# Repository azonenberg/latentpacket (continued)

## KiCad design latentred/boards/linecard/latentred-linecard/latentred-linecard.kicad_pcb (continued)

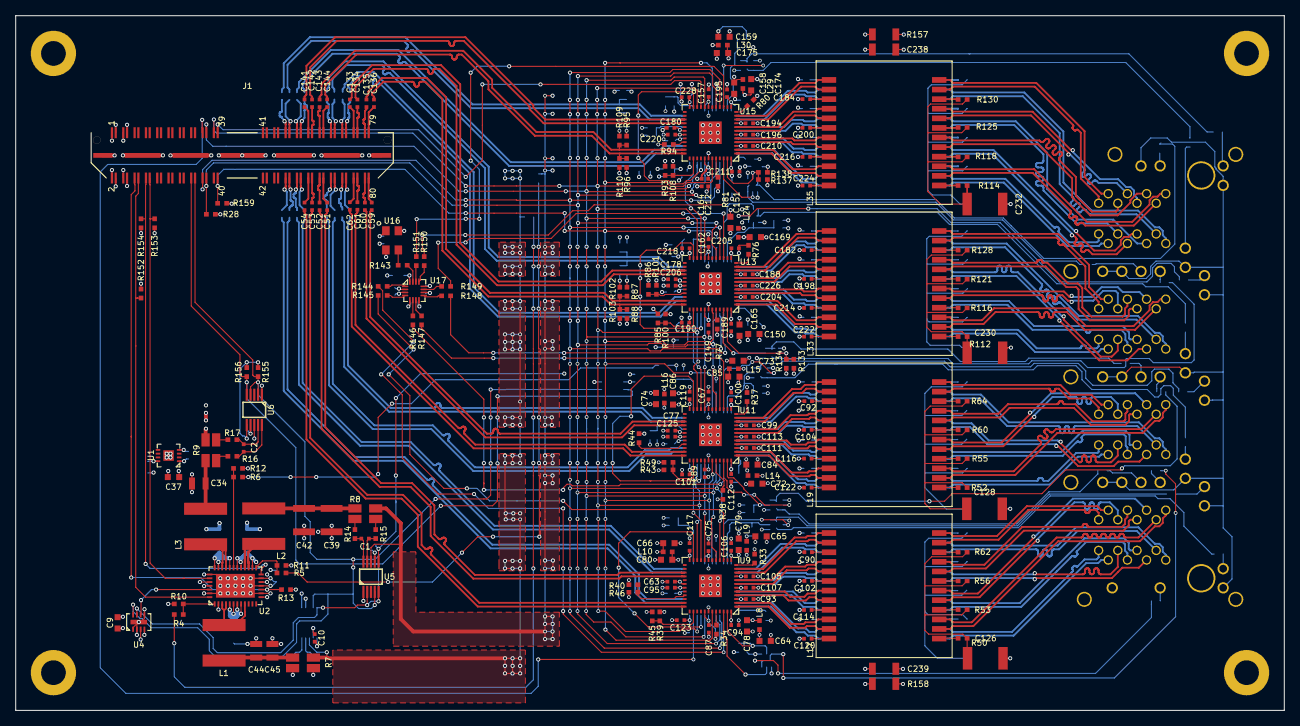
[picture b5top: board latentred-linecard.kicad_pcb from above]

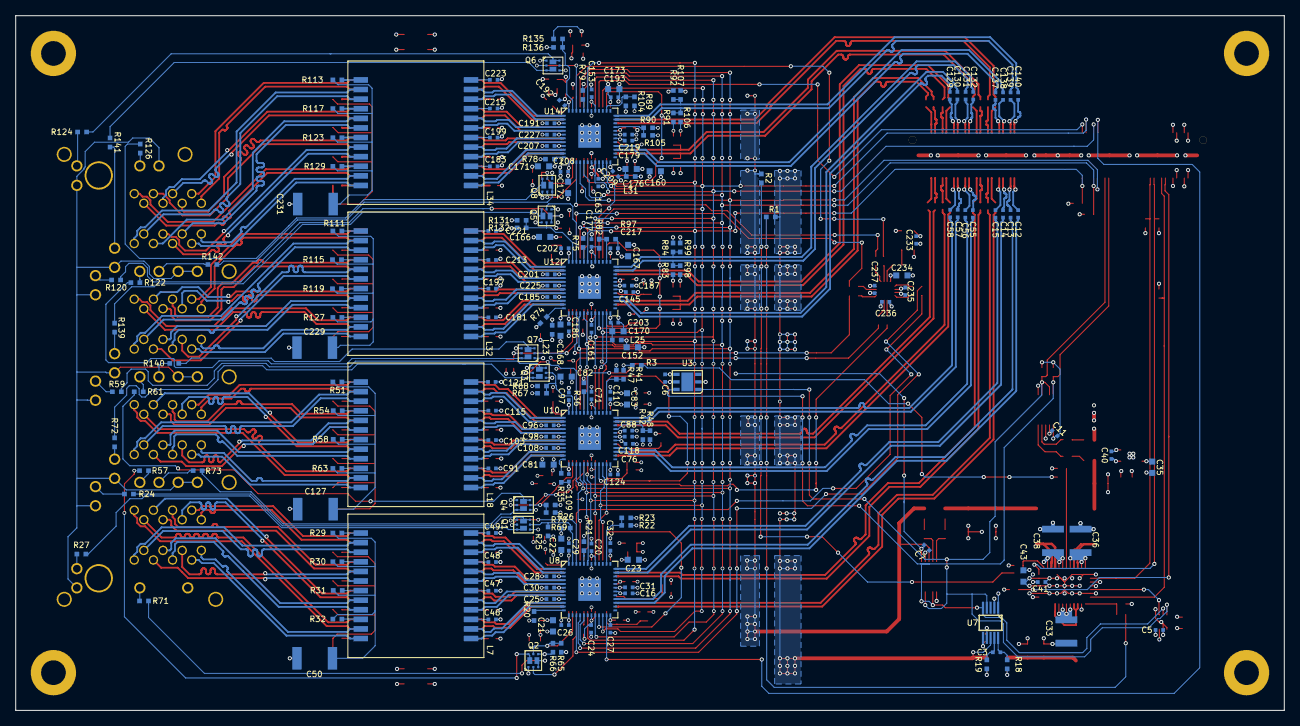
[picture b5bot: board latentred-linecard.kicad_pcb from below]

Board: 4 copper layers, 168.0 x 92.0 mm, 438 parts (211 on the bottom side), 425 nets.

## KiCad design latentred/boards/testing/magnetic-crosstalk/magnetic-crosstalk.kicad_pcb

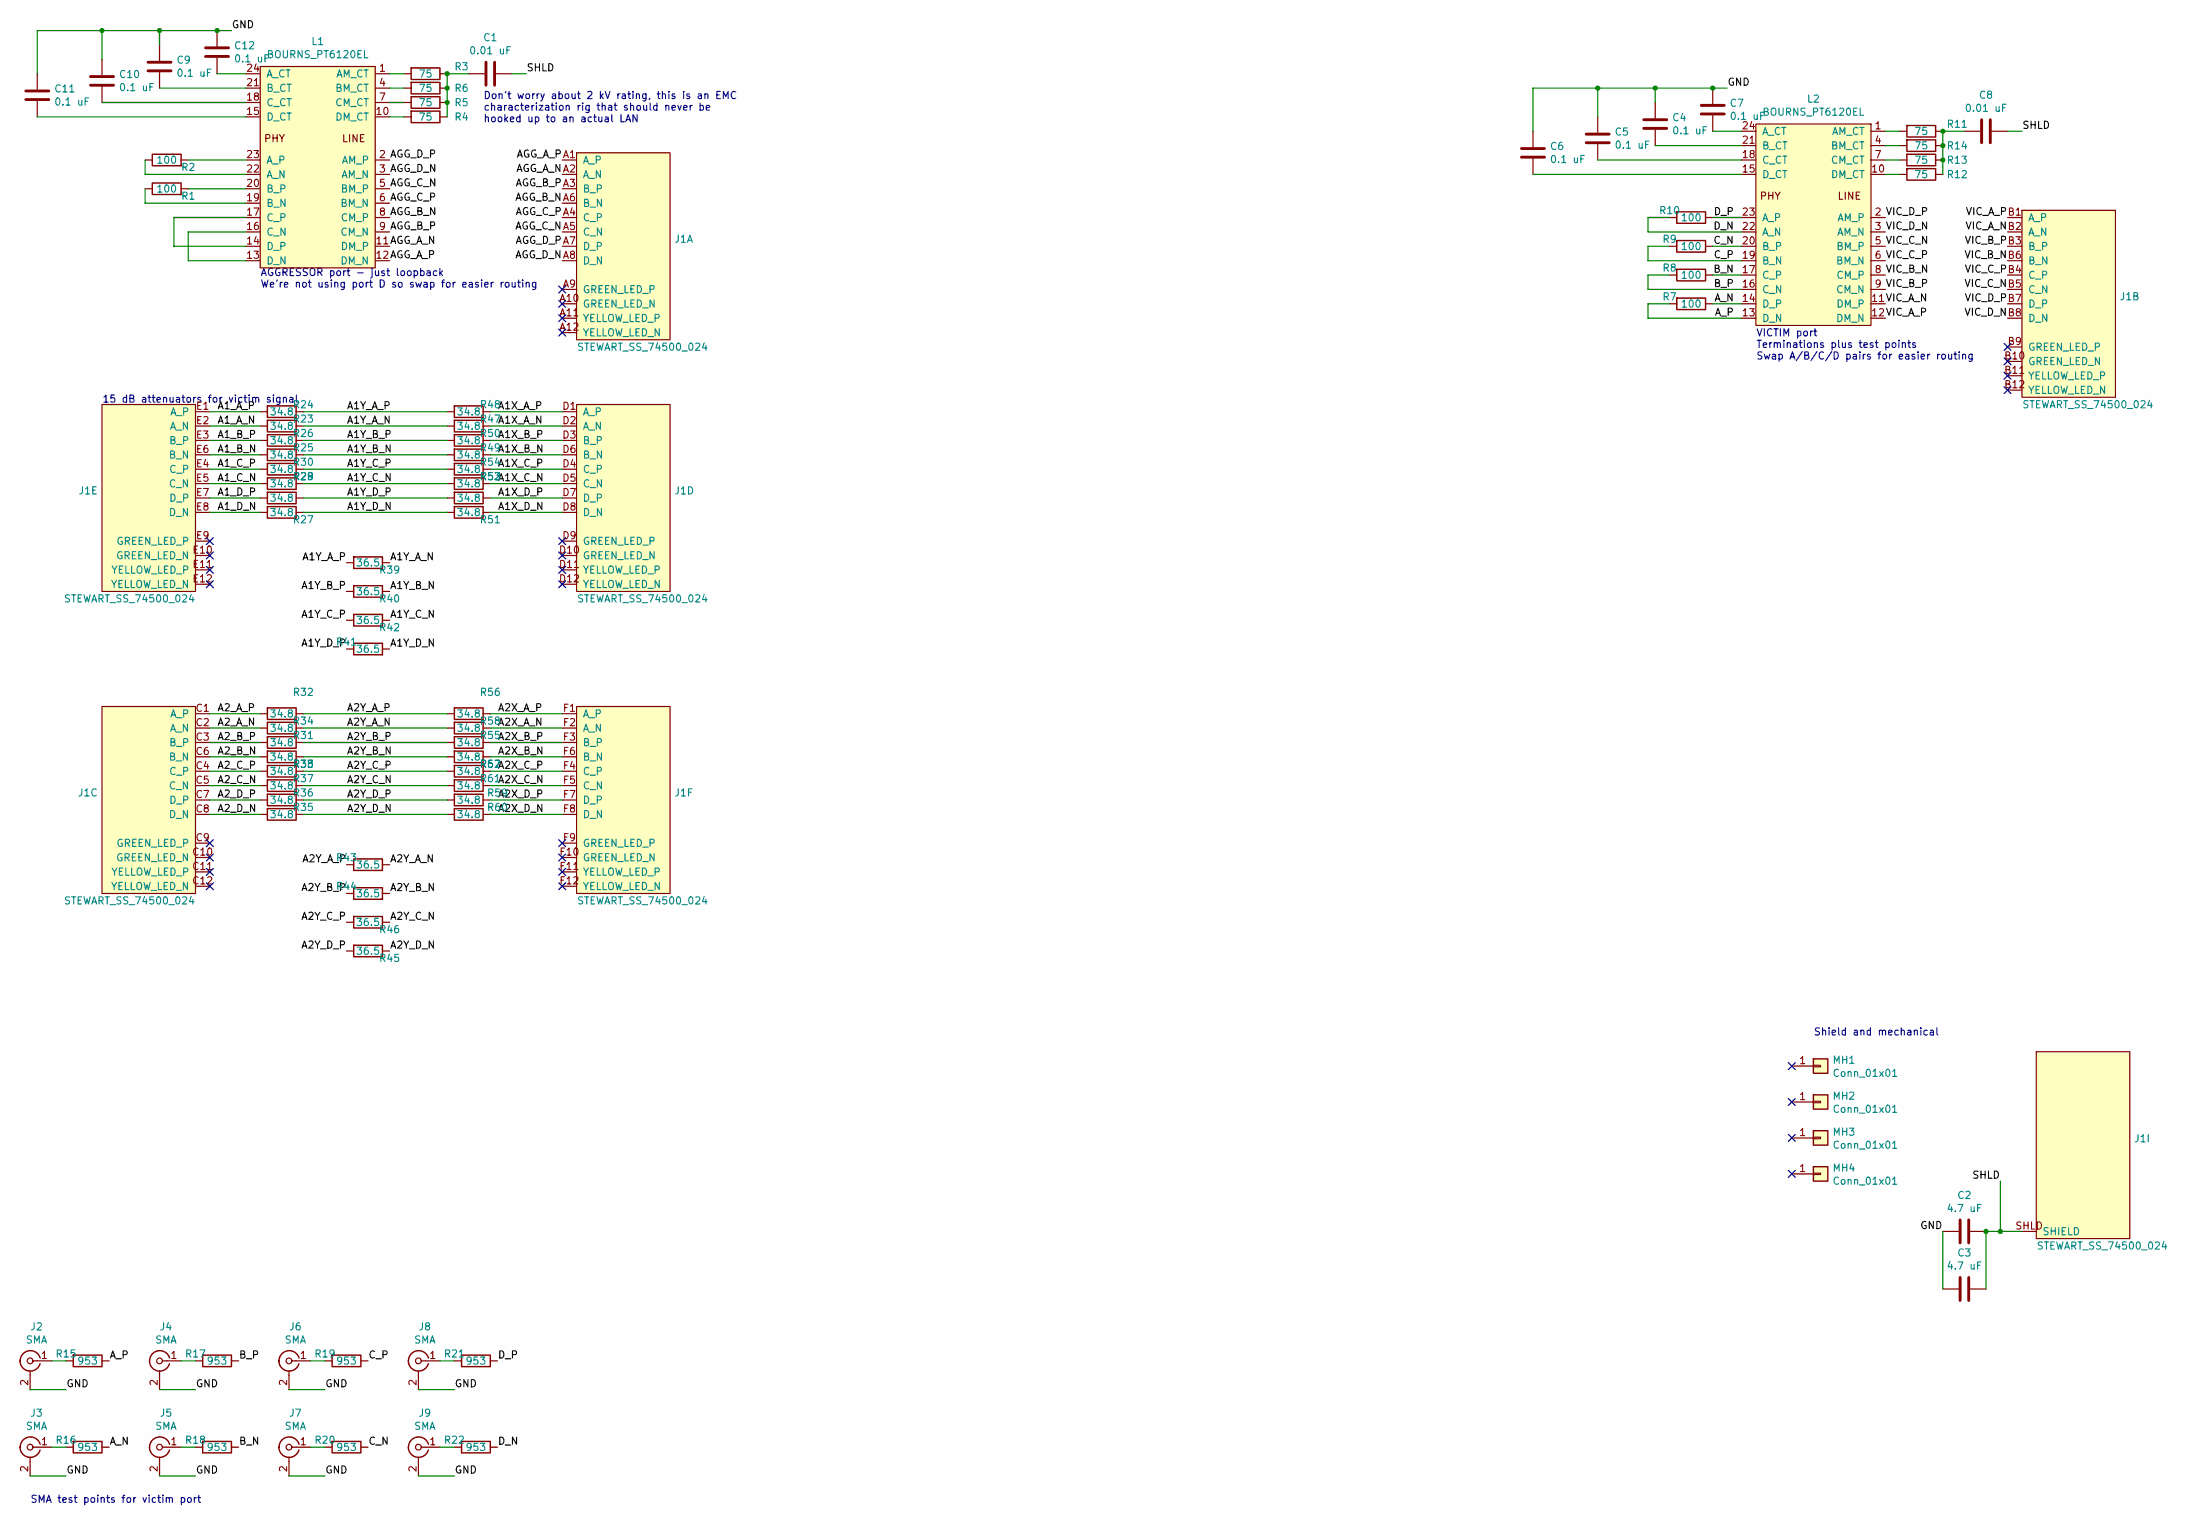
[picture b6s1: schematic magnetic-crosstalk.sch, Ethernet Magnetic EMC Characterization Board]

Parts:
C1, C8: 0.01 uF; EIA_0402_CAP_NOSILK
C2, C3: 4.7 uF; EIA_0603_CAP_NOSILK
C4, C5, C6, C7, C9, C10, C11, C12: 0.1 uF; EIA_0402_CAP_NOSILK
J1: STEWART_SS_74500_024; CONN_STEWART_SS_74500_024
J2, J3, J4, J5, J6, J7, J8, J9: SMA; CONN_SMA_EDGE_SAMTEC_SMA_J_P_H_ST_EM1
L1, L2: BOURNS_PT6120EL; BOURNS_PT61020EL
MH1, MH2, MH3, MH4: Conn_01x01; MECHANICAL_CLEARANCEHOLE_4_40
R1, R2, R7, R8, R9, R10: 100; EIA_0402_RES_NOSILK
R3, R4, R5, R6, R11, R12, R13, R14: 75; EIA_0402_RES_NOSILK
R15, R16, R17, R18, R19, R20, R21, R22: 953; EIA_0402_RES_NOSILK
R23, R24, R25, R26, R27, R28, R29, R30, R31, R32, R33, R34, R35, R36, R37, R38, R47, R48, R49, R50, R51, R52, R53, R54, R55, R56, R57, R58, R59, R60, R61, R62: 34.8; EIA_0402_RES_NOSILK
R39, R40, R41, R42, R43, R44, R45, R46: 36.5; EIA_0402_RES_NOSILK

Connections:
/A1X_A_N: J1.D2 (A_N), R48.1
/A1X_A_P: J1.D1 (A_P), R47.1
/A1X_B_N: J1.D6 (B_N), R50.1
/A1X_B_P: J1.D3 (B_P), R49.1
/A1X_C_N: J1.D5 (C_N), R54.1
/A1X_C_P: J1.D4 (C_P), R53.1
/A1X_D_N: J1.D8 (D_N), R51.1
/A1X_D_P: J1.D7 (D_P), R52.1
/A1Y_A_N: R24.1, R39.1, R48.2
/A1Y_A_P: R23.1, R39.2, R47.2
/A1Y_B_N: R26.1, R40.1, R50.2
/A1Y_B_P: R25.1, R40.2, R49.2
/A1Y_C_N: R30.1, R42.1, R54.2
/A1Y_C_P: R29.1, R42.2, R53.2
/A1Y_D_N: R27.1, R41.2, R51.2
/A1Y_D_P: R28.1, R41.1, R52.2
/A1_A_N: J1.E2 (A_N), R24.2
/A1_A_P: J1.E1 (A_P), R23.2
/A1_B_N: J1.E6 (B_N), R26.2
/A1_B_P: J1.E3 (B_P), R25.2
/A1_C_N: J1.E5 (C_N), R30.2
/A1_C_P: J1.E4 (C_P), R29.2
/A1_D_N: J1.E8 (D_N), R27.2
/A1_D_P: J1.E7 (D_P), R28.2
/A2X_A_N: J1.F2 (A_N), R55.1
/A2X_A_P: J1.F1 (A_P), R56.1
/A2X_B_N: J1.F6 (B_N), R57.1
/A2X_B_P: J1.F3 (B_P), R58.1
/A2X_C_N: J1.F5 (C_N), R62.1
/A2X_C_P: J1.F4 (C_P), R61.1
/A2X_D_N: J1.F8 (D_N), R60.1
/A2X_D_P: J1.F7 (D_P), R59.1
/A2Y_A_N: R31.1, R43.2, R55.2
/A2Y_A_P: R32.1, R43.1, R56.2
/A2Y_B_N: R33.1, R44.2, R57.2
/A2Y_B_P: R34.1, R44.1, R58.2
/A2Y_C_N: R38.1, R46.1, R62.2
/A2Y_C_P: R37.1, R46.2, R61.2
/A2Y_D_N: R36.1, R45.1, R60.2
/A2Y_D_P: R35.1, R45.2, R59.2
/A2_A_N: J1.C2 (A_N), R31.2
/A2_A_P: J1.C1 (A_P), R32.2
/A2_B_N: J1.C6 (B_N), R33.2
/A2_B_P: J1.C3 (B_P), R34.2
/A2_C_N: J1.C5 (C_N), R38.2
/A2_C_P: J1.C4 (C_P), R37.2
/A2_D_N: J1.C8 (D_N), R36.2
/A2_D_P: J1.C7 (D_P), R35.2
/AGG_A_N: J1.A2 (A_N), L1.11 (DM_P)
/AGG_A_P: J1.A1 (A_P), L1.12 (DM_N)
/AGG_B_N: J1.A6 (B_N), L1.8 (CM_P)
/AGG_B_P: J1.A3 (B_P), L1.9 (CM_N)
/AGG_C_N: J1.A5 (C_N), L1.5 (BM_P)
/AGG_C_P: J1.A4 (C_P), L1.6 (BM_N)
/AGG_D_N: J1.A8 (D_N), L1.3 (AM_N)
/AGG_D_P: J1.A7 (D_P), L1.2 (AM_P)
/A_N: L2.14 (D_P), R7.1, R16.1
/A_P: L2.13 (D_N), R7.2, R15.1
/B_N: L2.17 (C_P), R8.1, R18.1
/B_P: L2.16 (C_N), R8.2, R17.1
/C_N: L2.20 (B_P), R9.1, R20.1
/C_P: L2.19 (B_N), R9.2, R19.1
/D_N: L2.22 (A_N), R10.2, R22.1
/D_P: L2.23 (A_P), R10.1, R21.1
/GND: C2.2, C3.2, C4.1, C5.1, C6.1, C7.1, C9.1, C10.1, C11.1, C12.1, J2.2 (Ext), J3.2 (Ext), J4.2 (Ext), J5.2 (Ext), J6.2 (Ext), J7.2 (Ext), J8.2 (Ext), J9.2 (Ext)
/SHLD: C1.1, C2.1, C3.1, C8.1, J1.SHLD (SHIELD)
/VIC_A_N: J1.B2 (A_N), L2.11 (DM_P)
/VIC_A_P: J1.B1 (A_P), L2.12 (DM_N)
/VIC_B_N: J1.B6 (B_N), L2.8 (CM_P)
/VIC_B_P: J1.B3 (B_P), L2.9 (CM_N)
/VIC_C_N: J1.B5 (C_N), L2.5 (BM_P)
/VIC_C_P: J1.B4 (C_P), L2.6 (BM_N)
/VIC_D_N: J1.B8 (D_N), L2.3 (AM_N)
/VIC_D_P: J1.B7 (D_P), L2.2 (AM_P)
unnamed: C1.2, R3.1, R4.1, R5.1, R6.1
unnamed: C4.2, L2.21 (B_CT)
unnamed: C5.2, L2.18 (C_CT)
unnamed: C6.2, L2.15 (D_CT)
unnamed: C7.2, L2.24 (A_CT)
unnamed: C8.2, R11.1, R12.1, R13.1, R14.1
unnamed: C9.2, L1.21 (B_CT)
unnamed: C10.2, L1.18 (C_CT)
unnamed: C11.2, L1.15 (D_CT)
unnamed: C12.2, L1.24 (A_CT)
unnamed: J2.1 (In), R15.2
unnamed: J3.1 (In), R16.2
unnamed: J4.1 (In), R17.2
unnamed: J5.1 (In), R18.2
unnamed: J6.1 (In), R19.2
unnamed: J7.1 (In), R20.2
unnamed: J8.1 (In), R21.2
unnamed: J9.1 (In), R22.2
unnamed: L1.1 (AM_CT), R3.2
unnamed: L1.4 (BM_CT), R6.2
unnamed: L1.7 (CM_CT), R5.2
unnamed: L1.10 (DM_CT), R4.2
unnamed: L1.13 (D_N), L1.16 (C_N)
unnamed: L1.14 (D_P), L1.17 (C_P)
unnamed: L1.19 (B_N), R1.1
unnamed: L1.20 (B_P), R1.2
unnamed: L1.22 (A_N), R2.1
unnamed: L1.23 (A_P), R2.2
unnamed: L2.1 (AM_CT), R11.2
unnamed: L2.4 (BM_CT), R14.2
unnamed: L2.7 (CM_CT), R13.2
unnamed: L2.10 (DM_CT), R12.2

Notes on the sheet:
AGGRESSOR port - just loopback We're not using port D so swap for easier routing
Don't worry about 2 kV rating, this is an EMC characterization rig that should never be hooked up to an actual LAN
VICTIM port Terminations plus test points Swap A/B/C/D pairs for easier routing
15 dB attenuators for victim signal
Shield and mechanical
SMA test points for victim port

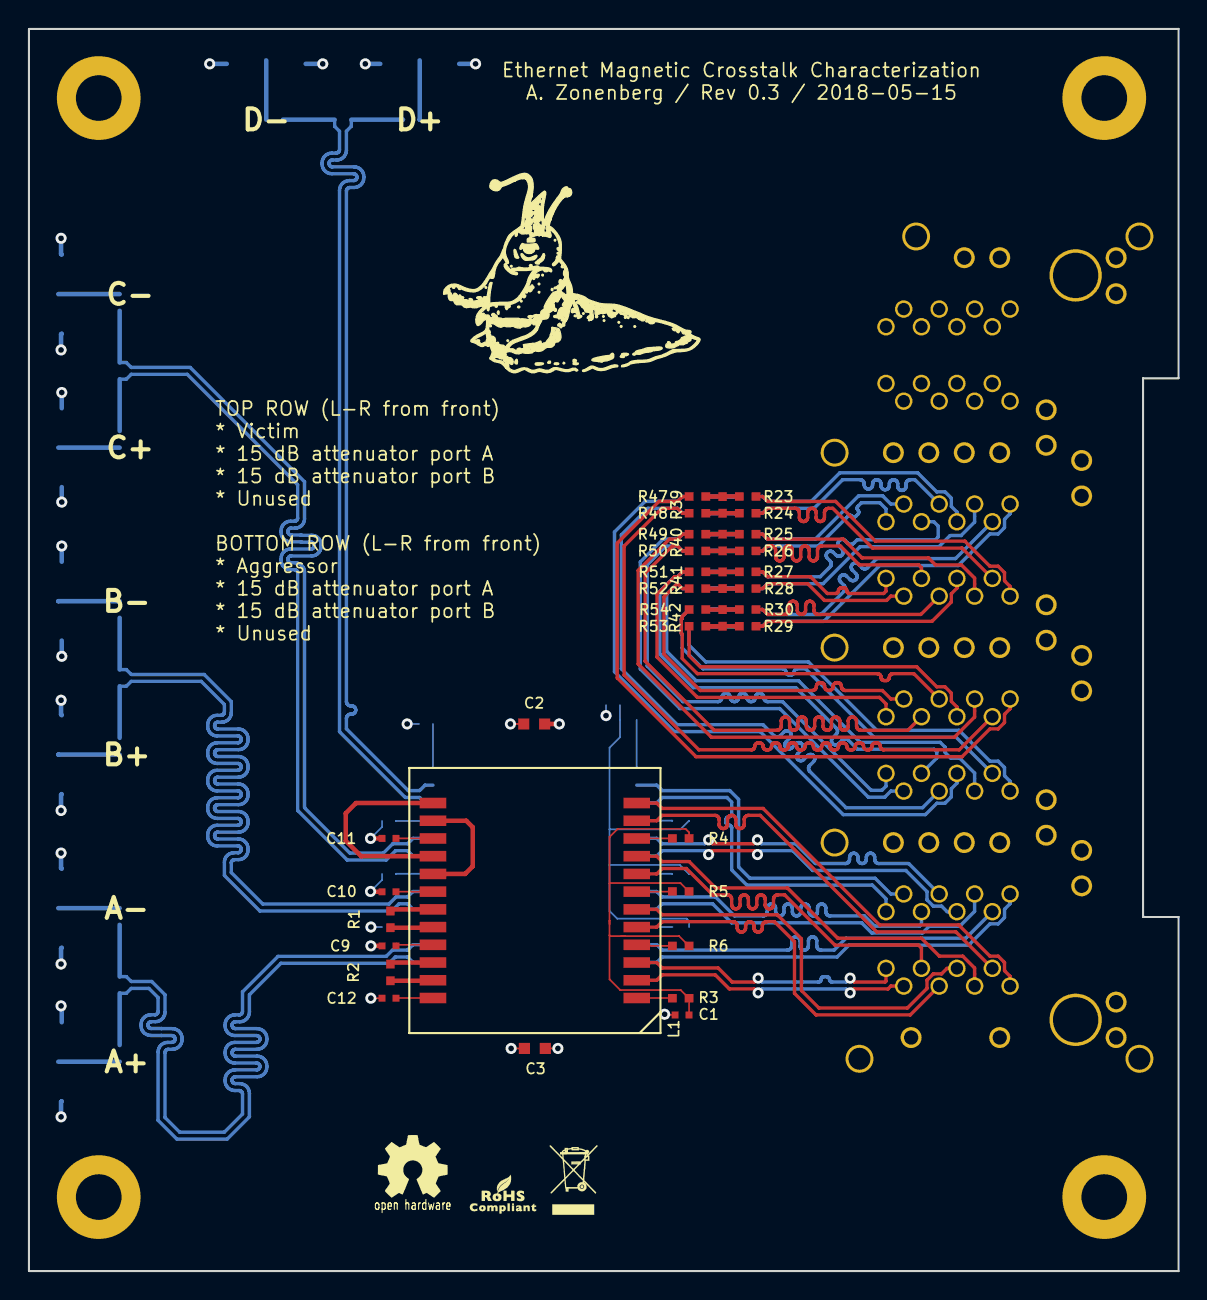
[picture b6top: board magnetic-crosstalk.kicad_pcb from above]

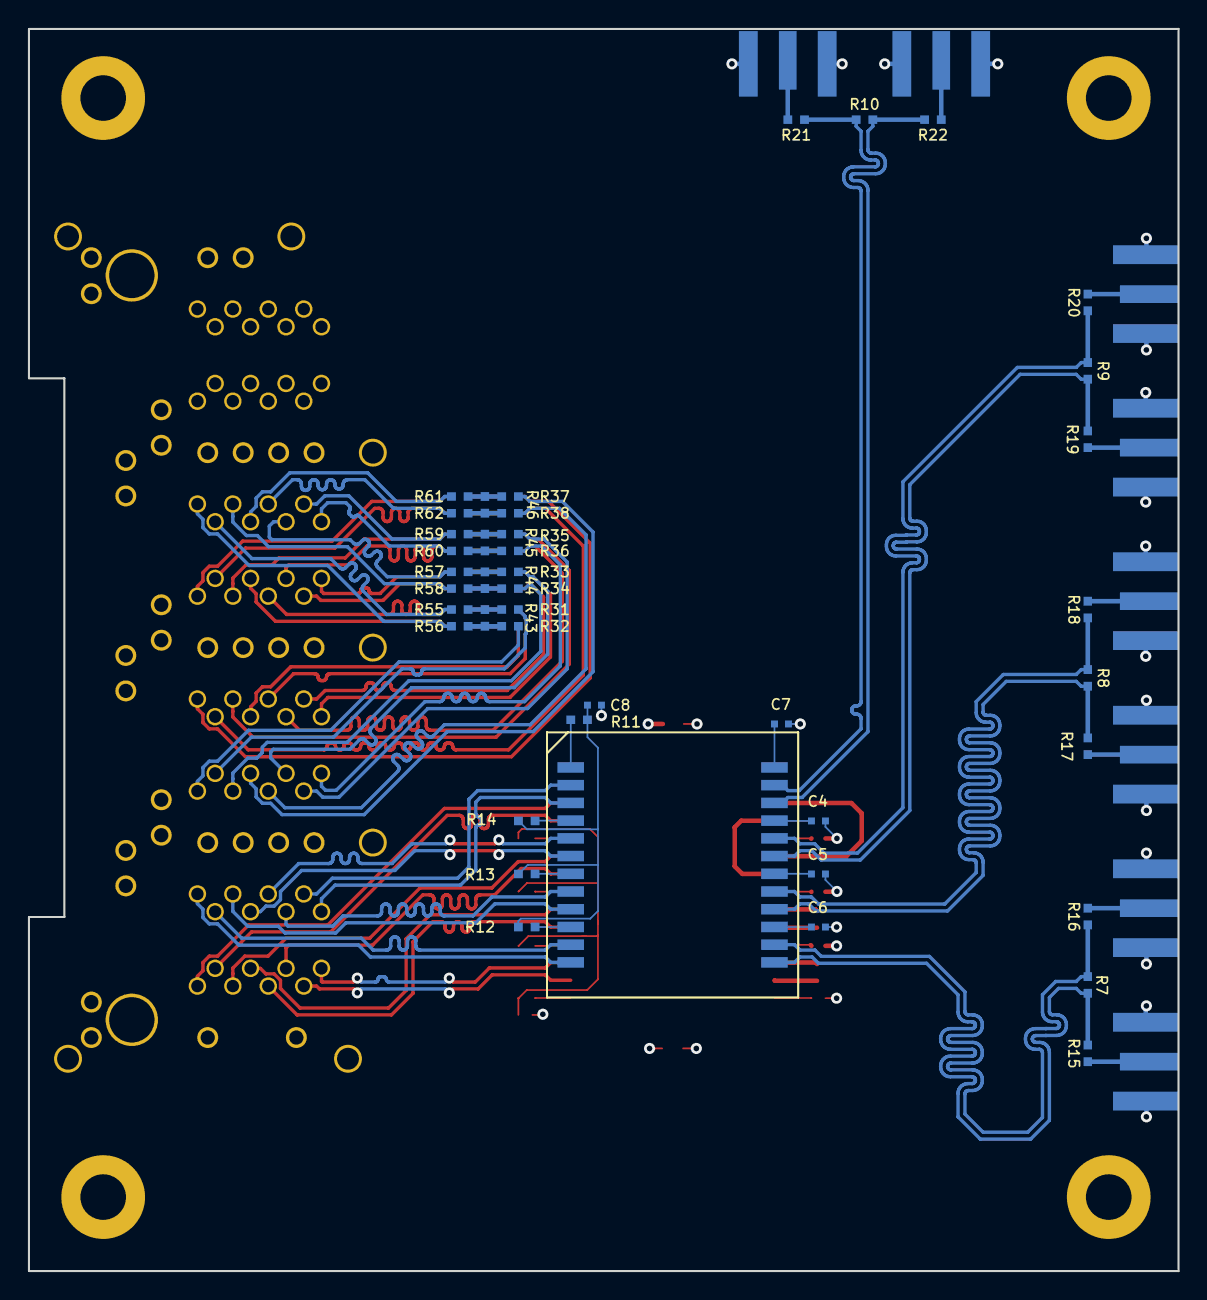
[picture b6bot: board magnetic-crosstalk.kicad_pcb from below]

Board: 4 copper layers, 82.4 x 89.0 mm, 89 parts (50 on the bottom side), 106 nets.

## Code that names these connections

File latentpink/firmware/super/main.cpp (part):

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void InitLog();
void DetectHardware();

void StartRail(GPIOPin& en, GPIOPin& pgood, uint32_t timeout, const char* name);
void StartSubRail(GPIOPin& en, GPIOPin& pgood, uint32_t timeout, const char* name);
void MonitorRail(GPIOPin& pgood, const char* name);
void PanicShutdown();

GPIOPin* g_en_12v0 = nullptr;
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	GPIOPin pwr_ok_led(&GPIOA, 0, GPIOPin::MODE_OUTPUT, GPIOPin::SLEW_SLOW);
	GPIOPin all_ok_led(&GPIOC, 14, GPIOPin::MODE_OUTPUT, GPIOPin::SLEW_SLOW);

	GPIOPin fpga_done(&GPIOB, 2, GPIOPin::MODE_INPUT, 0, false);
	GPIOPin mcu_rst_n(&GPIOB, 0, GPIOPin::MODE_OUTPUT, GPIOPin::SLEW_SLOW);
	GPIOPin fpga_rst_n(&GPIOA, 3, GPIOPin::MODE_OUTPUT, GPIOPin::SLEW_SLOW, 0, true);

	en_12v0 = 0;
	en_1v0 = 0;
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	gpio_led = 0;
	all_ok_led = 0;
	pwr_ok_led = 0;
	mcu_rst_n = 0;
	fpga_rst_n = 0;

	//Save pointers to all the rails for use in other functions
	g_en_12v0 = &en_12v0;
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	//All power rails came up if we get here
	g_log("Power is good, releasing FPGA reset\n");
	pwr_ok_led = 1;
	fpga_rst_n = 1;

	//Everything started up if we get here
	//TODO: wait for heartbeat from MCU too
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/**
	@brief Polls a power rail and look for signs of trouble
 */
void MonitorRail(GPIOPin& pgood, const char* name)
{
	if(!pgood)
	{
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/**
	@brief Turns on a single power rail, checking for failure
 */
void StartRail(GPIOPin& en, GPIOPin& pgood, uint32_t timeout, const char* name)
{
	g_log("Turning on %s\n", name);

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/**
	@brief Turns on a sub-rail switched or regulated from a parent rail, but lacking its own PGOOD output
 */
void StartSubRail(GPIOPin& en, GPIOPin& pgood, uint32_t timeout, const char* name)
{
	//These rails have no PGOOD feedback.
	//If it overcurrents, it will probably drag down the parent rail so check for faults over a fixed time window
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
void InitUART()
{
	//Initialize the UART for local console: 115.2 Kbps using PB6 for USART2 transmit and PB7 for USART2 receive
	//TODO: nice interface for enabling UART interrupts
	GPIOPin uart_tx(&GPIOB, 6, GPIOPin::MODE_PERIPHERAL, GPIOPin::SLEW_SLOW, 0);
	GPIOPin uart_rx(&GPIOB, 7, GPIOPin::MODE_PERIPHERAL, GPIOPin::SLEW_SLOW, 0);
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
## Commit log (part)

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2018-04-16 Initial schematic skeleton for LATENTRED 1G line card
2018-04-17 Continued work on line card design. Now have PSU and all PHYs, still working on clock distribution.
2018-04-19 Finished initial footprint creation, ready to begin layout
2018-04-23 Continued initial layout, mostly on PHY indicator LEDs.
2018-04-24 Completely rerouted magnetics for much cleaner, though slightly wider, "clamshell" layout
2018-04-25 Continued PHY layout
2018-04-27 Initial layout on ports 2/3
2018-04-28 Removed meanders from MDI traces as per Intel layout manual. Now only doing skew matching.
2018-04-30 Initial version of crosstalk evaluation board
2018-05-15 Began updating magnetic-crosstalk board for v0.2
2018-05-15 Fixed pinout bugs. v0.2 PCB release.
2018-06-01 Added hash collision Monte Carlo simulation
2018-06-02 Initial notes on architecture
2018-06-05 Continued initial line card layout
2018-06-11 Added antikernel-ipcores submodule
2018-06-15 Initial work on MACAddressTable. Not finished.
2018-06-15 Continued initial MAC table implementation
2018-06-17 Continued routing line card PCB
2018-06-17 Fixed several bugs in MAC table
2019-08-14 Continued initial skeleton firmware
2019-08-14 initial string printing
2019-08-14 Initial work on switch API
2019-08-14 Added lots more commands to switch API
2019-08-15 Initial skeleton of CLI structs
2019-08-15 Initial work on CLI. Still polling UART, no ISRs yet.
2019-08-16 Continued various IRQ cleanup etc
2019-08-16 Initial gitattributes
2019-08-16 Updated linguist properties for LATENTRED firmware
2019-08-17 Continued initial CLI work. Gave up on newlib because none of stdio was working.
2019-08-17 Continued initial CLI parser work
2019-08-17 Continued work on CLI. Can now insert text in the middle of a token, but deletion still needs work.
2019-08-17 Initial right-arrow-key handling
2019-08-17 Continued work on arrow keys
2019-08-17 More work on spacebar handling
2019-08-18 Improved backspace handling in the middle of tokens
2019-08-18 Backspace at the start of a token now merges left properly
2019-08-18 Initial implementation of Cisco-style command completion. Cannot yet tab complete, and ? doesn't work, but fully typed commands are correctly decoded.
2019-08-18 Renamed some files for more consistent naming. Added fno-rtti and new/delete stubs to prevent linker problems when using destructors.
2019-08-19 Continued initial work on switch object model
2019-08-19 Initial implementation of LatentRedManagementPort. Started moving switchapi stuff over to OO model
2019-08-20 More work on cppstubs for better global variable support. The config we have right here works.
2019-08-20 Continued debugging new global setup
2019-08-20 Continued refactoring, rewrote _start in C++
2019-08-20 Continued C++-ification
2019-08-20 Lots of bug fixes, including proper handling of init_array. Fixed new UART location
2019-08-20 Continued building out initial object model
2019-08-21 Initial skeleton of management board HDL
2019-08-21 Initial skeleton of FPGA bitstream for INTEGRALSTICK management
2019-08-21 Re-enabled stuff we turned off for debug
2019-08-22 Continued work on integration of FPGA and MCU for "show ver"
2019-08-22 Pushing current debug state
2019-08-22 Updated gitattributes for vivado project
2019-08-22 CLI: now actually call "show hardware". Disabled parser debug prints
2019-08-22 Fixed missing print
2019-08-23 Initial implementation of LTC3374 temperature sensor readout
2019-08-23 Initial work on CharacterDevice API
2019-08-25 Initial work on SPI support for MCU-FPGA link
2019-08-25 Fixed SPI data size
2019-08-25 Fixed bug where ManagementController did not properly reset
2019-08-26 Initial implementation of "show int status"
2019-09-02 Miscellaneous debugging and new printout logic in "show hardware"
2019-09-02 Added fp cache
2019-09-02 Updated ignore properties for generated IP files
2019-09-02 MACAddressTable: converted a bunch of stuff to use SV structs
2019-09-03 Refactoring of MACAddressTable, added management ports (not yet used for anything). Fixed some bugs in learning logic causing pend_wr_en to be set for too long.
2019-09-03 MACAddressTable: implemented management interface
2019-09-03 Initial skeletons of SwitchFabric and GigabitRxFifo. Still needs lots of work.
2019-09-03 Continued work on RxFifo. Renamed it since now it's being used for 10G interfaces too.
2019-09-04 Continued work on RxFifo, began work on sim testbench for it
2019-09-05 Continued work on RX FIFO
2019-09-05 RxFifo: moved output signals into a struct
2019-09-05 Continued initial implementation of SwitchFabric
2019-09-05 More work on broadcast handling
2019-09-06 Initial work on top level module for switch
2019-09-07 Fixed bug where RxFifo sent an extra dummy word after end of frame
2019-09-07 Continued initial work on SwitchFabric. Successfully forwarded one frame during testing.
2019-09-07 Fixed unintended latch
2019-09-07 Cleanup of temporary variables
2019-09-09 Began work on GigabitRxFifo
2019-09-10 GigabitRxFifo now has all input ports in one clock domain
2019-09-10 Initial skeleton of switch engine schematic
2019-09-10 Initial switch engine power budgeting
2019-09-16 Initial block diagram
2019-09-16 Reset fixes
2019-09-18 Continued work on VCU118 testing. Added pipeline stage to SwitchFabric to improve timing.
2019-09-29 Fixed a bunch of bugs in RxFifo
2019-09-29 SwitchFabric now properly forwards ethertypes
2019-10-11 OutputFifo: don't send extra word at end of frame
2022-12-19 Initial skeleton of single-phy-sma-host board. Ready for layout.
2022-12-19 Updated single-phy-sma-host with stitching vias and final layout
2022-12-19 Initial version of single-phy-sma-device
2023-01-29 Fixed incorrect LED level shifter connections
2023-04-16 Initial work on LATENTPINK
2023-04-16 Updated submodules
2023-04-17 Fixed formatting
2023-04-23 Continued initial schematic capture and floorplanning
2023-05-10 Continued work on schematic, mostly power supply and QDR
2023-05-11 Initial version of RGMII PHY schematic
2023-05-16 Switched to new RJ45 for LATENTPINK, continued general PHY schematic
2023-05-17 Rearranged ports, added center tap capacitors
2023-05-18 Continued initial component placement
2023-05-21 Finished initial schematic, ready for design review
2023-05-21 Continued work on signoff review, added some more test points and SFP+ activity LEDs
2023-05-23 Preliminary routing of first four baseT interfaces on VSC8512
2023-05-24 Continued layout of VSC8512
2023-05-28 Lots of layout progress on bottom power/management/supervisor area
2023-05-28 Continued work on management MCU area
2023-05-29 Routed upper SGMII PHY except for bus to FPGA
2023-05-29 Hooked up some more PHY stuff plus management UART transceiver
2023-05-30 Moved QDR to wide orientation, preliminary layout (no length matching) of C/A bus
2023-05-30 VSC8512 LED layout
2023-06-02 Lots more layout of low speed stuff and power. Partial layout of 1.2V supply. Initial RGMII escape routing.
2023-06-03 Routing of northwest corner
2023-06-03 Good progress routing QDR with new pinout
2023-06-04 Continued initial QDR routing
2023-06-04 Initial routing of Vtt/Vref supply
2023-06-05 Continued routing of last few control/power signals. 23 unrouted, some 1.8V decoupling and one thermal sensor
2023-06-06 Initial QDR length matching
2023-06-07 Fixed DRC violations in QDR, added stitching vias, various cleanup
2023-06-08 Removed unused simulations
2023-06-14 Added more simulations
2023-06-14 Initial skeleton HDL file
2023-06-15 Continued initial RTL and constraint skeleton for PCB validation
2023-06-19 Continued RTL development
2023-06-19 Updated PCB layout with changes made during initial FPGA RTL dev
2023-06-20 Continued initial work on FPGA design skeleton
2023-06-22 Continued initial work on IngressCDC
2023-06-25 Updated ignore properties, added another waveform configuration for simulation
2023-06-25 Hopefully final LATENTPINK PCB layout for quote
2023-06-26 Updated ignore properties for PCB
2023-06-26 Floorplanning and clock buffering tweaks to RX
2023-06-27 Initial implementation of VlanUntagger
2023-06-29 Lots more simulation updates, continued work on ingress FIFO. Fixed missing dummy VIO on SFP+ interface. Refactored all MAC/PCS blocks to new NetworkInterfaces module
2023-06-30 Updated v0.1b design to have NPTH for heatsink attachment
2023-07-04 Added submodules needed by MCU firmware
2023-07-04 Initial work on LATENTPINK forwarding engine
2023-07-04 Initial skeleton code for simulation testbench for CLI
2023-07-04 Continued initial skeleton work on CLI
2023-07-06 Continued initial work on simulation firmware. Can now serialize microkvs data to file so configs persist across simuilation restarts
2023-07-07 Zero fill hostname on startup to avoid uninitialized cells at end
2023-07-08 Continued work on management interface, initial FPGA-side support for setting VLAN and trunk mode over management interface
2023-07-09 Added "show flash detail"
2023-07-09 Continued initial work on commit/rollback
2023-07-10 Initial staticnet integration, simulation firmware is now pingable
2023-07-10 Initial SSH server integration
2023-07-11 Added pipeline stage to MACAddressTable garbage collection
2023-07-11 Add SSH server key generation
2023-07-13 Initial work on integration of crypto accelerator with staticnet ssh
2023-07-13 Switched 250 MHz clock to a BUFH, more floorplan tweaks
2023-07-16 Initial skeleton supervisor firmware. Just an LED blinky and initializing timer and UART
2023-07-16 Make output directory if it doesn't already exist
2023-07-16 Finished initial supervisor firmware for rail bringup
2023-07-16 Initial skeleton code for main MCU firmware
2023-07-20 Continued work on sensor bringup
2023-07-20 Added SRAM MBIST
2023-07-21 Successful bringup of RGMII PHY to the point it can respond to MDIO traffic and receive frames on the FPGA. No path to MCU yet.
2023-07-23 Incoming Ethernet frames on management interface are now passed to stack; outbound send path not implemented yet
2023-07-23 Initial SSH is functional
2023-07-24 Added pipeline delay for cross clock path
2023-07-24 Dual key generation test
2023-07-24 Added a lot of CLI commands, not all fully implemented
2023-07-25 IP configuration via CLI now works and can be persisted to flash
2023-07-25 Added "show register" and "show mmd" commands
2023-07-26 Added LogSink so we can get log messages echoed to SSH sessions
2023-07-26 Fixed bug causing multiple SSH session states to share a single set of crypto state, leading to older sessions being dropped when a new one came in
2023-07-27 Added more DP83867 test patterns
2023-07-30 Continued QSGMII PHY bringup
2023-07-31 Added BISTMuxes module, continued debug of forwarding path
2023-08-03 Lots of debugging and work on fabric. Appears to be correctly handling frames up to the output of the ForwardingEngine
2023-08-03 Removed some debug code, timing tweaks
2023-08-07 Initial implementation of "show temp"
2023-08-08 Continued switch debug, fixed off-by-one in >PREFETCH_DEPTH sized packets
2023-08-10 Updating ipcores with fixed elastic buffer in GigBaseXPCS
2023-08-11 Continued debugging hang when ping flooding
2023-08-12 Fixed race condition causing packet corruption or port hangs after ~1M packets in a short time frame
2023-08-13 Initial WIP readout of performance counters via QSPI. Haven't tested yet as no clientside code to access it.
2023-08-13 Initial work on performance counter resets
2023-08-13 Implemented clearing of performance counters
2023-08-14 Reduced performance counter width to 48 bits
2023-08-14 More area optimization of performance counters, improved packing density
2023-09-26 Added JTAG server run script
2023-09-26 Fixed bug where QSPI register interface would corrupt bits 3/4 of MDIO register address
2023-09-28 Fixes to timing constraints, update to latest ipcores
2023-10-04 Fixed CDC issue in management link up flag
